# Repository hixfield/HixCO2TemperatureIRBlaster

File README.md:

![Build with PlatformIO](https://img.shields.io/badge/build%20with-PlatformIO-orange?logo=data%3Aimage%2Fsvg%2Bxml%3Bbase64%2CPHN2ZyB3aWR0aD0iMjUwMCIgaGVpZ2h0PSIyNTAwIiB2aWV3Qm94PSIwIDAgMjU2IDI1NiIgeG1sbnM9Imh0dHA6Ly93d3cudzMub3JnLzIwMDAvc3ZnIiBwcmVzZXJ2ZUFzcGVjdFJhdGlvPSJ4TWlkWU1pZCI+PHBhdGggZD0iTTEyOCAwQzkzLjgxIDAgNjEuNjY2IDEzLjMxNCAzNy40OSAzNy40OSAxMy4zMTQgNjEuNjY2IDAgOTMuODEgMCAxMjhjMCAzNC4xOSAxMy4zMTQgNjYuMzM0IDM3LjQ5IDkwLjUxQzYxLjY2NiAyNDIuNjg2IDkzLjgxIDI1NiAxMjggMjU2YzM0LjE5IDAgNjYuMzM0LTEzLjMxNCA5MC41MS0zNy40OUMyNDIuNjg2IDE5NC4zMzQgMjU2IDE2Mi4xOSAyNTYgMTI4YzAtMzQuMTktMTMuMzE0LTY2LjMzNC0zNy40OS05MC41MUMxOTQuMzM0IDEzLjMxNCAxNjIuMTkgMCAxMjggMCIgZmlsbD0iI0ZGN0YwMCIvPjxwYXRoIGQ9Ik0yNDkuMzg2IDEyOGMwIDY3LjA0LTU0LjM0NyAxMjEuMzg2LTEyMS4zODYgMTIxLjM4NkM2MC45NiAyNDkuMzg2IDYuNjEzIDE5NS4wNCA2LjYxMyAxMjggNi42MTMgNjAuOTYgNjAuOTYgNi42MTQgMTI4IDYuNjE0YzY3LjA0IDAgMTIxLjM4NiA1NC4zNDYgMTIxLjM4NiAxMjEuMzg2IiBmaWxsPSIjRkZGIi8+PHBhdGggZD0iTTE2MC44NjkgNzQuMDYybDUuMTQ1LTE4LjUzN2M1LjI2NC0uNDcgOS4zOTItNC44ODYgOS4zOTItMTAuMjczIDAtNS43LTQuNjItMTAuMzItMTAuMzItMTAuMzJzLTEwLjMyIDQuNjItMTAuMzIgMTAuMzJjMCAzLjc1NSAyLjAxMyA3LjAzIDUuMDEgOC44MzdsLTUuMDUgMTguMTk1Yy0xNC40MzctMy42Ny0yNi42MjUtMy4zOS0yNi42MjUtMy4zOWwtMi4yNTggMS4wMXYxNDAuODcybDIuMjU4Ljc1M2MxMy42MTQgMCA3My4xNzctNDEuMTMzIDczLjMyMy04NS4yNyAwLTMxLjYyNC0yMS4wMjMtNDUuODI1LTQwLjU1NS01Mi4xOTd6TTE0Ni41MyAxNjQuOGMtMTEuNjE3LTE4LjU1Ny02LjcwNi02MS43NTEgMjMuNjQzLTY3LjkyNSA4LjMyLTEuMzMzIDE4LjUwOSA0LjEzNCAyMS41MSAxNi4yNzkgNy41ODIgMjUuNzY2LTM3LjAxNSA2MS44NDUtNDUuMTUzIDUxLjY0NnptMTguMjE2LTM5Ljc1MmE5LjM5OSA5LjM5OSAwIDAgMC05LjM5OSA5LjM5OSA5LjM5OSA5LjM5OSAwIDAgMCA5LjQgOS4zOTkgOS4zOTkgOS4zOTkgMCAwIDAgOS4zOTgtOS40IDkuMzk5IDkuMzk5IDAgMCAwLTkuMzk5LTkuMzk4em0yLjgxIDguNjcyYTIuMzc0IDIuMzc0IDAgMSAxIDAtNC43NDkgMi4zNzQgMi4zNzQgMCAwIDEgMCA0Ljc0OXoiIGZpbGw9IiNFNTcyMDAiLz48cGF0aCBkPSJNMTAxLjM3MSA3Mi43MDlsLTUuMDIzLTE4LjkwMWMyLjg3NC0xLjgzMiA0Ljc4Ni01LjA0IDQuNzg2LTguNzAxIDAtNS43LTQuNjItMTAuMzItMTAuMzItMTAuMzItNS42OTkgMC0xMC4zMTkgNC42Mi0xMC4zMTkgMTAuMzIgMCA1LjY4MiA0LjU5MiAxMC4yODkgMTAuMjY3IDEwLjMxN0w5NS44IDc0LjM3OGMtMTkuNjA5IDYuNTEtNDAuODg1IDIwLjc0Mi00MC44ODUgNTEuODguNDM2IDQ1LjAxIDU5LjU3MiA4NS4yNjcgNzMuMTg2IDg1LjI2N1Y2OC44OTJzLTEyLjI1Mi0uMDYyLTI2LjcyOSAzLjgxN3ptMTAuMzk1IDkyLjA5Yy04LjEzOCAxMC4yLTUyLjczNS0yNS44OC00NS4xNTQtNTEuNjQ1IDMuMDAyLTEyLjE0NSAxMy4xOS0xNy42MTIgMjEuNTExLTE2LjI4IDMwLjM1IDYuMTc1IDM1LjI2IDQ5LjM2OSAyMy42NDMgNjcuOTI2em0tMTguODItMzkuNDZhOS4zOTkgOS4zOTkgMCAwIDAtOS4zOTkgOS4zOTggOS4zOTkgOS4zOTkgMCAwIDAgOS40IDkuNCA5LjM5OSA5LjM5OSAwIDAgMCA5LjM5OC05LjQgOS4zOTkgOS4zOTkgMCAwIDAtOS4zOTktOS4zOTl6bS0yLjgxIDguNjcxYTIuMzc0IDIuMzc0IDAgMSAxIDAtNC43NDggMi4zNzQgMi4zNzQgMCAwIDEgMCA0Ljc0OHoiIGZpbGw9IiNGRjdGMDAiLz48L3N2Zz4=)

Hardware (schematic and PCB) and software for a WIFI connected device offering lots of functionality: CO2 measuring, IR Transmitter, IR receiver and temperature sensor.
As output it has an OLED display, and RGB LED and beeper. Its based on the ESP8266 microcontroller and tts part of my home automation system based on a raspberry pi running Mosquitoo, Nodered, InfluxDB and Grafana.

## Improvements
- [ ] Add temperature offset in firware (seams device is reading hotter then ambient?)
- [ ] Switch to a passive buzzer (should get rid of the reset beeping)
- [ ] Add PCB jumper (solder) to endable/disable buzzer
- [ ] Configuration of WIFI SSID/PWD via web interface
- [ ] Extend firmware to support learning IR codes
- [ ] Extend firmware for remote sending on AC commands

## Brief overview

- Schematic and PCB design in Eagle
- WIFI connected
- MQTT firmware written using PlatformIO
- Plugs in the mains (no need for any USB seperate power brick)
- IR output: PCB has 3 possible positions for the IR Led just use the one convenient for you
- IR input (can be usefull to learn IR codes)
- measures the room temperature via DS18B20
- RGB Led to show green-orange-red depending on CO2 concentration
- Beeper on board
- 32x128 OLED dispaly
- based on popular [ESP8266](http://esp8266.com)

## Youtube movies

| 3D case design in Fusion 360.    | Putting case and PCB together                                     |
|---------------------------------------|-----------------------------------------|
||

# overview

# Hardware

[Click here for hardware information](hardware/README.md)

# Software

[Click here for software information](software/README.md)

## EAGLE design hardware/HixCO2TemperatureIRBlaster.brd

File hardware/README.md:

# HixCO2TemperatureIRBlaster - Hardware
The respository contains the EagleCAD file + JLCPCB zip export (in the `/hardware` folder)

| Top                                 | Bottom                                 |
|-------------------------------------|----------------------------------------|
|  |  |

# BOM
## Base
| ID                                 | Part                                                                |
|------------------------------------|----------------------------------------------------------------------
|B1                                  | BUZZER(12MM)     
|C1, C2                              | 47uF (SMD 1206)             
|C3, C5                              | 100nF (SMD 1206)           
|C6                                  | 680uF/6.3V 
|F1                                  | Fuse 800mA 250V       
|J1                                  | Header female 6 pin
|J2                                  | IEC320C8 mains connector         
|J3                                  | Header female 4 pin or XH4P             
|Q1                                  | Mosfet AO3400           
|R2, R7, R10, R11, R15               | 10K (SMD 1206)             
|R9                                  | 4.7K (SMD 1206)
|R12                                 | 2.2K (SMD 1206)  
|R14                                 | S10K275          
|S3, S4                              | SMD Push button     
|U$2                                 | ESP8266(ESP12E)V2
|U$3                                 | RGB LED 5mm          
|U1                                  | TSOP2238      
|U2                                  | LM3940 (SMD)         
|U3                                  | HLK-PM01 (mains to 5v powerbrick)     
|U4                                  | DS18B20 *Eventhough I have designed the PCB to allow mounting a plain TO-92 DS18B20 externally, it seams to be highly inaccurate because (I suspect) it takes over the heat via its leads from the internal of the case/pcb. Therefore it is better to use an external DS18B20 probe. I have included a case design for a plain TO-92 and external sensor probe (with strain relief).*

## IR blasting (optional)
| ID                                 | Part                                                                |
|------------------------------------|----------------------------------------------------------------------
|L1, L2, L3                          | IR LED 100 mA.    -> only assemble the one that points in the direction right for you!
|Q2                                  | Mosfet AO3400           
|R1, R3, R6                          | 68 Ohm (SMD 1206) -> only assemble for the LED that points in the direction right for you!                
|R5                                  | 10K (SMD 1206)       

## IR receiving (optional)
| ID                                 | Part                                                                |
|------------------------------------|----------------------------------------------------------------------
|C4                                  | 4.7uF (SMD 1206) 
|R8                                  | 100 Ohm (SMD 1206)          
|U1                                  | TSOP2238      

# Schematic
The repository contains the EagleCAD (in the `/hardware` folder)

# 3D printed case
(the repository contains the stl files (`/hardware/case` folder)

## external DS18B20 sensor probe
| base                                     | lid                                           |
|------------------------------------------|-----------------------------------------------|
|  |       |
|      |  |

## plain TO-92 DS18B20 sensor

| base                                     | lid                                           |
|------------------------------------------|-----------------------------------------------|
|  |       |
|      |  |

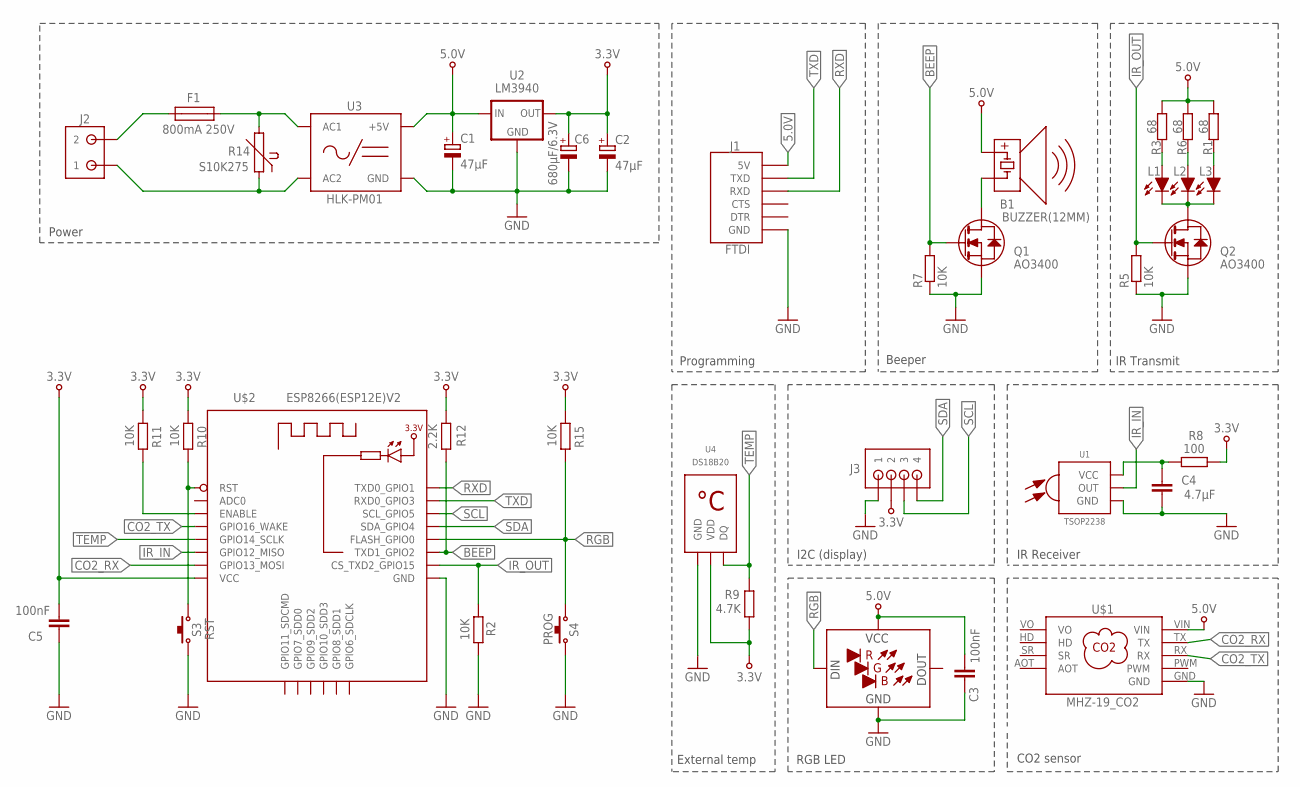
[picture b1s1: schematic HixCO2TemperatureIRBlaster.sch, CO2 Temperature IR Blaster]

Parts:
B1: BUZZER(12MM)
C1, C2: 47μF; SMC_A
C3, C5: 100nF; C1206
C4: 4.7μF; C1206
C6: 680μF/6.3V; ELKO_RADIAL_STRAIGHT_4P_8D_9H
F1: 800mA 250V; FUSE_508
J1: FTDI
J2: IEC320C8
J3: XH4P
L1, L2, L3: LEDLED5MM_ANGLED1; LED5MM_ANGLED1
Q1, Q2: AO3400; SOT23
R1, R3, R6: 68; 0204/7
R2, R5, R7, R10, R11, R15: 10K; R1206
R8: 100; R1206
R9: 4.7K; R1206
R12: 2.2K; R1206
R14: S10K275
S3: RST; SMDPUSHBTN_TYPE1
S4: PROG; SMDPUSHBTN_TYPE1
U1: TSOP2238
U2: LM3940; SOT223
U3: HLK-PM01
U4: DS18B20; TO-92(123)
U$1: MHZ-19_CO2
U$2: ESP8266(ESP12E)V2; ESP8266(ESP12E)
U$3: LED_RGB; LED_PL9823-F5

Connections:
3.3V: C2.+, C5.1, C6.+, J3.2, R8.2, R9.2, R10.2, R11.2, R12.2, R15.2, U2.3 (OUT), U4.3 (VDD), U$2.VCC
5.0V: B1.+, C1.+, C3.1, J1.5V, R1.2, R3.2, R6.2, U2.1 (IN), U3.VO+ (+5V), U$1.VIN, U$3.VCC
AC2: J2.AC1 (1), R14.1, U3.AC2
BEEP: Q1.1 (G), R7.2, R12.1, U$2.GPIO2_TXD1 (TXD1_GPIO2)
CO2_RX: U$1.TX, U$2.GPIO13_MOSI
CO2_TX: U$1.RX, U$2.GPIO16_WAKE
GND: C1.-, C2.-, C3.2, C4.2, C5.2, C6.-, J1.GND, J3.1, Q1.2 (S), Q2.2 (S), R2.1, R5.1, R7.1, S3.2, S4.2, U1.GND, U2.2 (GND), U2.4 (GND), U3.VO- (GND), U4.1 (GND), U$1.GND, U$2.GND, U$3.GND
IR_IN: U1.OUT, U$2.GPIO12_MISO
IR_OUT: Q2.1 (G), R2.2, R5.2, U$2.GPIO15_CS_TXD2 (CS_TXD2_GPIO15)
unnamed: F1.2, R14.2, U3.AC1
unnamed: F1.1, J2.AC2 (2)
unnamed: L1.CATHODE (C), L2.CATHODE (C), L3.CATHODE (C), Q2.3 (D)
unnamed: L2.ANODE (A), R6.1
unnamed: B1.-, Q1.3 (D)
unnamed: C4.1, R8.1, U1.VCC
unnamed: R10.1, S3.1, U$2.RST
unnamed: R11.1, U$2.ENABLE
unnamed: L1.ANODE (A), R3.1
unnamed: L3.ANODE (A), R1.1
RGB: R15.1, S4.1, U$2.GPIO0_FLASH (FLASH_GPIO0), U$3.DIN
RXD: J1.RXD, U$2.GPIO1_TXD0 (TXD0_GPIO1)
SCL: J3.3, U$2.GPIO5_SCL (SCL_GPIO5)
SDA: J3.4, U$2.GPIO4_SDA (SDA_GPIO4)
TEMP: R9.1, U4.2 (DQ), U$2.GPIO14_SCLK
TXD: J1.TXD, U$2.GPIO3_RXD0 (RXD0_GPIO3)
VO: U$1.VO

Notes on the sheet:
Power
Programming
Beeper
External temp
IR Transmit
I2C (display)
IR Receiver
CO2 sensor
RGB LED

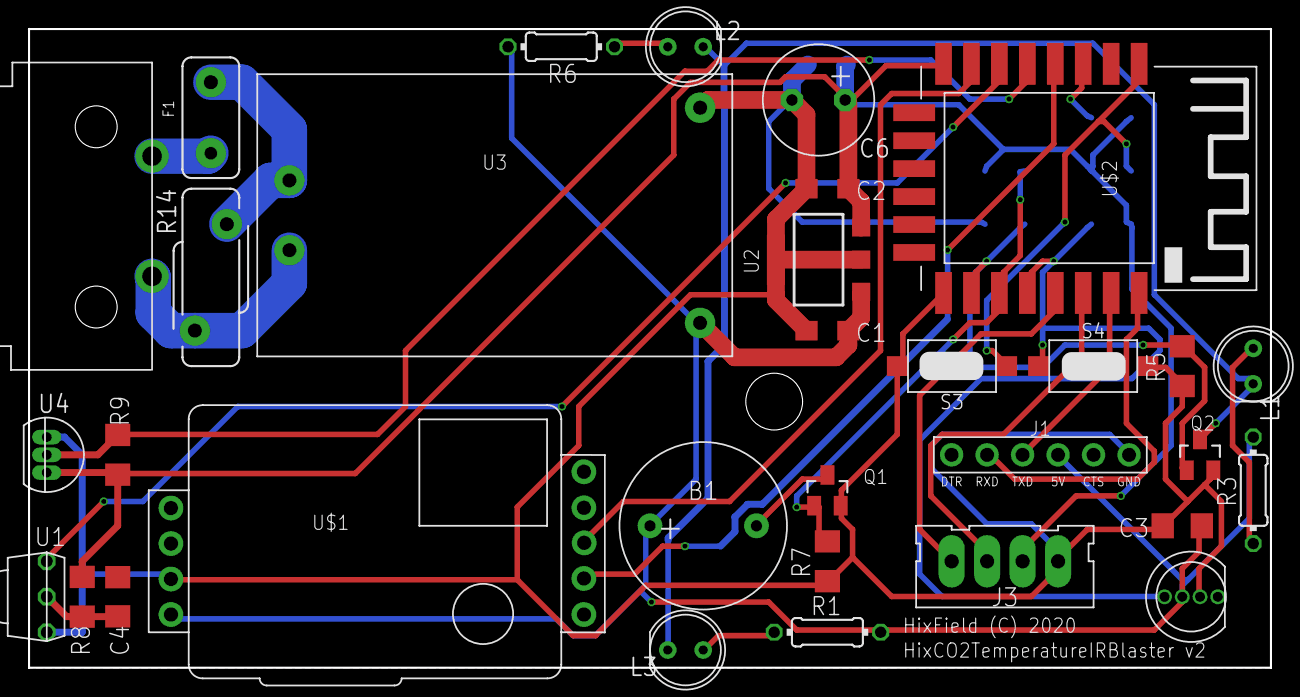
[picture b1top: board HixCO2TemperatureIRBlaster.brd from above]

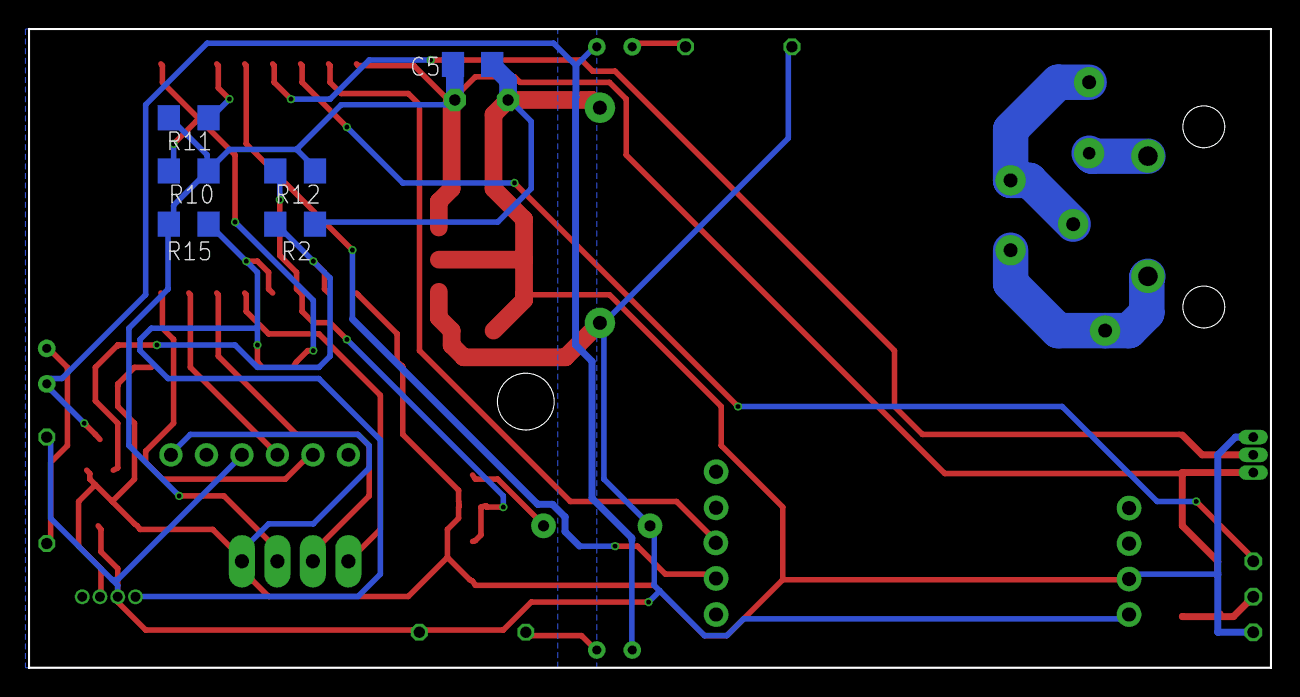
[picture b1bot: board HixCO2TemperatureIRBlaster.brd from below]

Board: 2 copper layers, 88.9 x 45.7 mm, 38 parts (6 on the bottom side), 25 nets.

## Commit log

2020-03-02 added hardware
2020-03-03 update hardware
2020-03-04 continued working on hardware models
2020-03-06 updated esp pin mapping
2020-03-08 electronic hardware v1 complete
2020-03-08 added gitignore
2020-03-30 added board testing software version
2020-04-01 all hw connections tested and working
2020-04-02 continued working
2020-04-03 IR issue solved (solder bridge!)
2020-04-03 removed AC test code
2020-04-04 Fixed short-circuit between 3.3V and 5.0V on board layout
2020-04-05 added jlcpbc export zip
2020-04-10 fixed html page issue and led now complete black when disabled via html config
2020-04-16 flipped top image
2020-04-17 updated documentation
2020-04-17 updated doc for software
2020-04-17 update software readme
2020-04-17 dimmed the RGB led
2020-04-17 added firmware define to disable the IR IN (seams to make firware unstable -> sudden resets?)
2020-04-18 check if CO2 value is valid added reset info the config page
2020-04-19 removed dynamic allocations in MQTT to try to make firmware more stable...
2020-12-04 update sampling rate to 1 minute
2020-12-04 no message
2020-12-04 fixed influxdb pubishing
2020-12-04 updated version to 2.0.3
2020-12-13 update readme split bom
2020-12-13 updated flash settings
2020-12-23 removed IR stuff, bumped to v2.1.0
2020-12-23 cleanup folders
2020-12-23 removed obsolete image
2020-12-25 added device info to config page and calibration options
2020-12-27 wifi_mac published
2020-12-28 added info and case for external DS18B20 probe
2020-12-29 added build timestamp to mqtt data
2021-01-17 added transparant image
2021-01-22 added co2 scale correction factor
2021-05-14 updated version of ESP8266 in platformio + bumped version
2021-08-27 added reset timeout for mqtt connection
2022-07-03 now using HixDS18B20
2022-07-03 minor tweaks
2022-07-06 led now white if no MQTT connection (blue means no wifi connection now)
2022-07-06 bumped version

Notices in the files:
hardware/HixCO2TemperatureIRBlaster.brd:
HixField (C) 2020
